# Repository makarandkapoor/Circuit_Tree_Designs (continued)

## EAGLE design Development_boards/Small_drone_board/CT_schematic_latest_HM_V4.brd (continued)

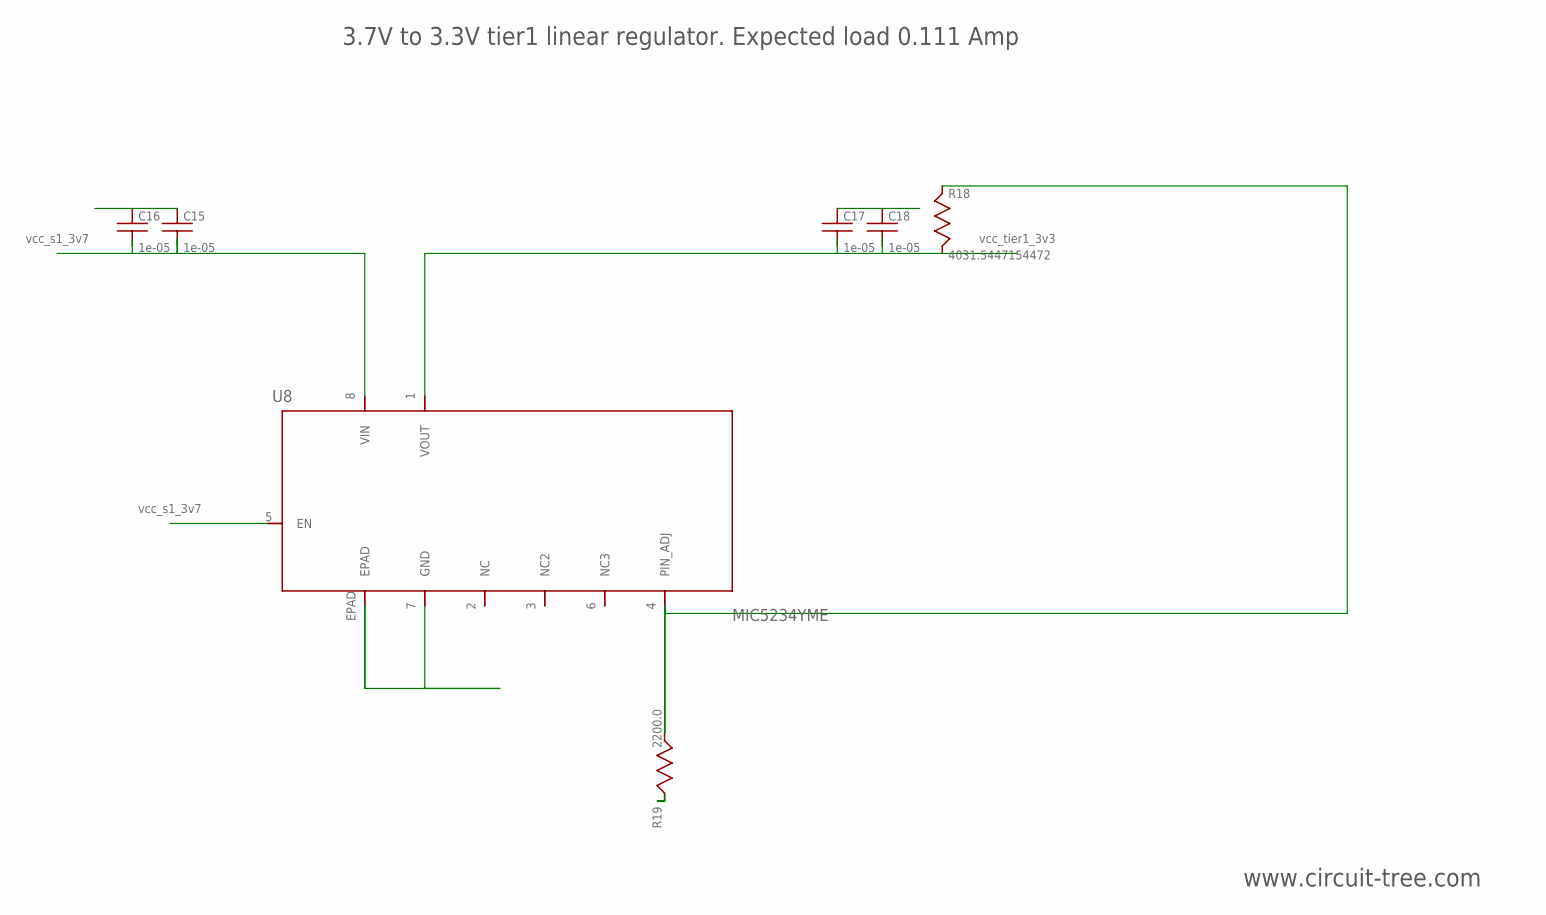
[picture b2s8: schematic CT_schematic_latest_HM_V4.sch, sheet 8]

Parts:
C15, C16, C17, C18: 1e-05; C1210
R18: 4031.5447154472; R0603
R19: 2200.0; R0603
U8: MIC5234YME; SOIC-8_EP

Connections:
GND: C15.2, C16.2, C17.2, C18.2, R19.2, U8.7 (GND), U8.EPAD; also elsewhere on the board
NET_U8_4: R18.2, R19.1, U8.4 (PIN_ADJ)
VCC_S1_3V7: C15.1, C16.1, U8.5 (EN), U8.8 (VIN); also elsewhere on the board
VCC_TIER1_3V3: C17.1, C18.1, R18.1, U8.1 (VOUT); also elsewhere on the board

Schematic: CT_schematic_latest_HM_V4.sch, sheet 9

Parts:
C19: 1e-07; C0402
R20, R21: 10000.0; R0603
R22: 9100.0; R0603
R23: 680000.0; R0603
R24: 120000.0; R0603
U11: TPS3895ADRYR; SON-6

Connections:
GND: C19.2, R22.2, R24.2, U11.2 (GND); also elsewhere on the board
NET_U11_1: R21.1, R22.1, U11.1 (ENABLE)
NET_U11_3: R23.2, R24.1, U11.3 (SENSE)
NET_U11_4: R20.1, U11.4 (SENSE_OUT); also elsewhere on the board
VCC_TIER1_3V3: C19.1, R20.2, R21.2, R23.1, U11.6 (VCC); also elsewhere on the board

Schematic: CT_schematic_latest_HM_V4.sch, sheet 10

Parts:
C20, C21: 1e-05; C1206
R25: 2000.0; R0603
R26: 10000.0; R0603
U9: MCP73831T-2ACI/MC; DFN8_2X3MC
U10: S2B-PH-SM4-TB(LF)(SN); JST-2-SMD

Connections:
GND: C20.2, C21.2, R25.2, U9.6 (VSS), U9.9 (EP), U10.2 (TP2); also elsewhere on the board
INPUT_USBPOWER_5V: C20.1, R26.2, U9.1 (VDD), U9.2 (VDD2); also elsewhere on the board
NET_U9_5: R26.1, U9.5 (STAT)
NET_U9_8: R25.1, U9.8 (PROG)
VCC_S1_3V7: C21.1, U9.3 (VBAT), U9.4 (VBAT2), U10.1 (TP1); also elsewhere on the board

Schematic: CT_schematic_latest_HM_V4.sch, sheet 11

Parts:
C22, C23, C24: 1e-08; C0402
R2: 1000.0; R0603
U12: 4-1437565-2; SW_4-1437565-2
U13: Q65110A2395; LGM67K-G1J2-24-Z
U14, U15, U16: nc7sz125m5x; NC7SZ125M5X

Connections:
GND: C22.2, C23.2, C24.2, R2.2, U13.C, U14.2 (A), U14.3 (GND), U15.1 (OE1_B), U15.3 (GND), U16.1 (OE1_B), U16.3 (GND); also elsewhere on the board
NET_U1_4: U16.4 (Y); also elsewhere on the board
NET_U1_27: U13.A; also elsewhere on the board
NET_U1_28: U12.3 (POLE2), U12.4 (POLE22); also elsewhere on the board
NET_U4_11: U15.4 (Y); also elsewhere on the board
NET_U11_4: U14.4 (Y), U15.2 (A), U16.2 (A); also elsewhere on the board
NET_U12_1: R2.1, U12.1 (POLE1), U12.2 (POLE12)
RST_OUT_U2_JTAG_RST_B: U14.1 (OE1_B); also elsewhere on the board
VCC_TIER1_3V3: C22.1, C23.1, C24.1, U14.5 (VCC), U15.5 (VCC), U16.5 (VCC); also elsewhere on the board

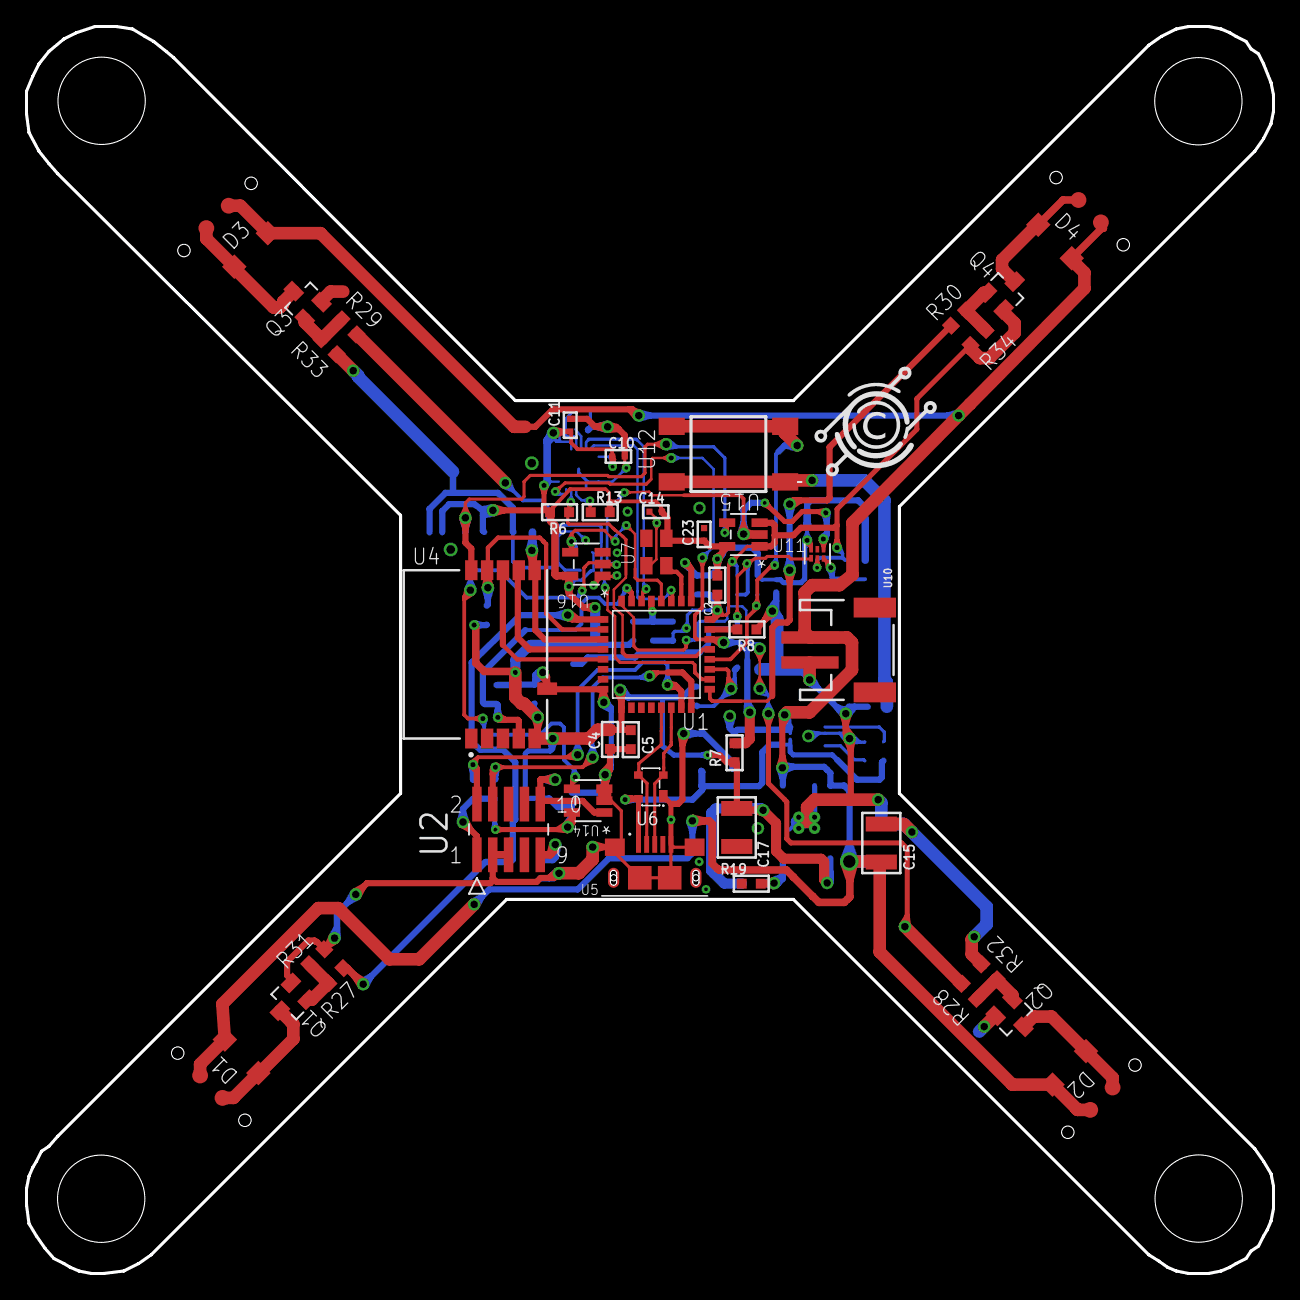
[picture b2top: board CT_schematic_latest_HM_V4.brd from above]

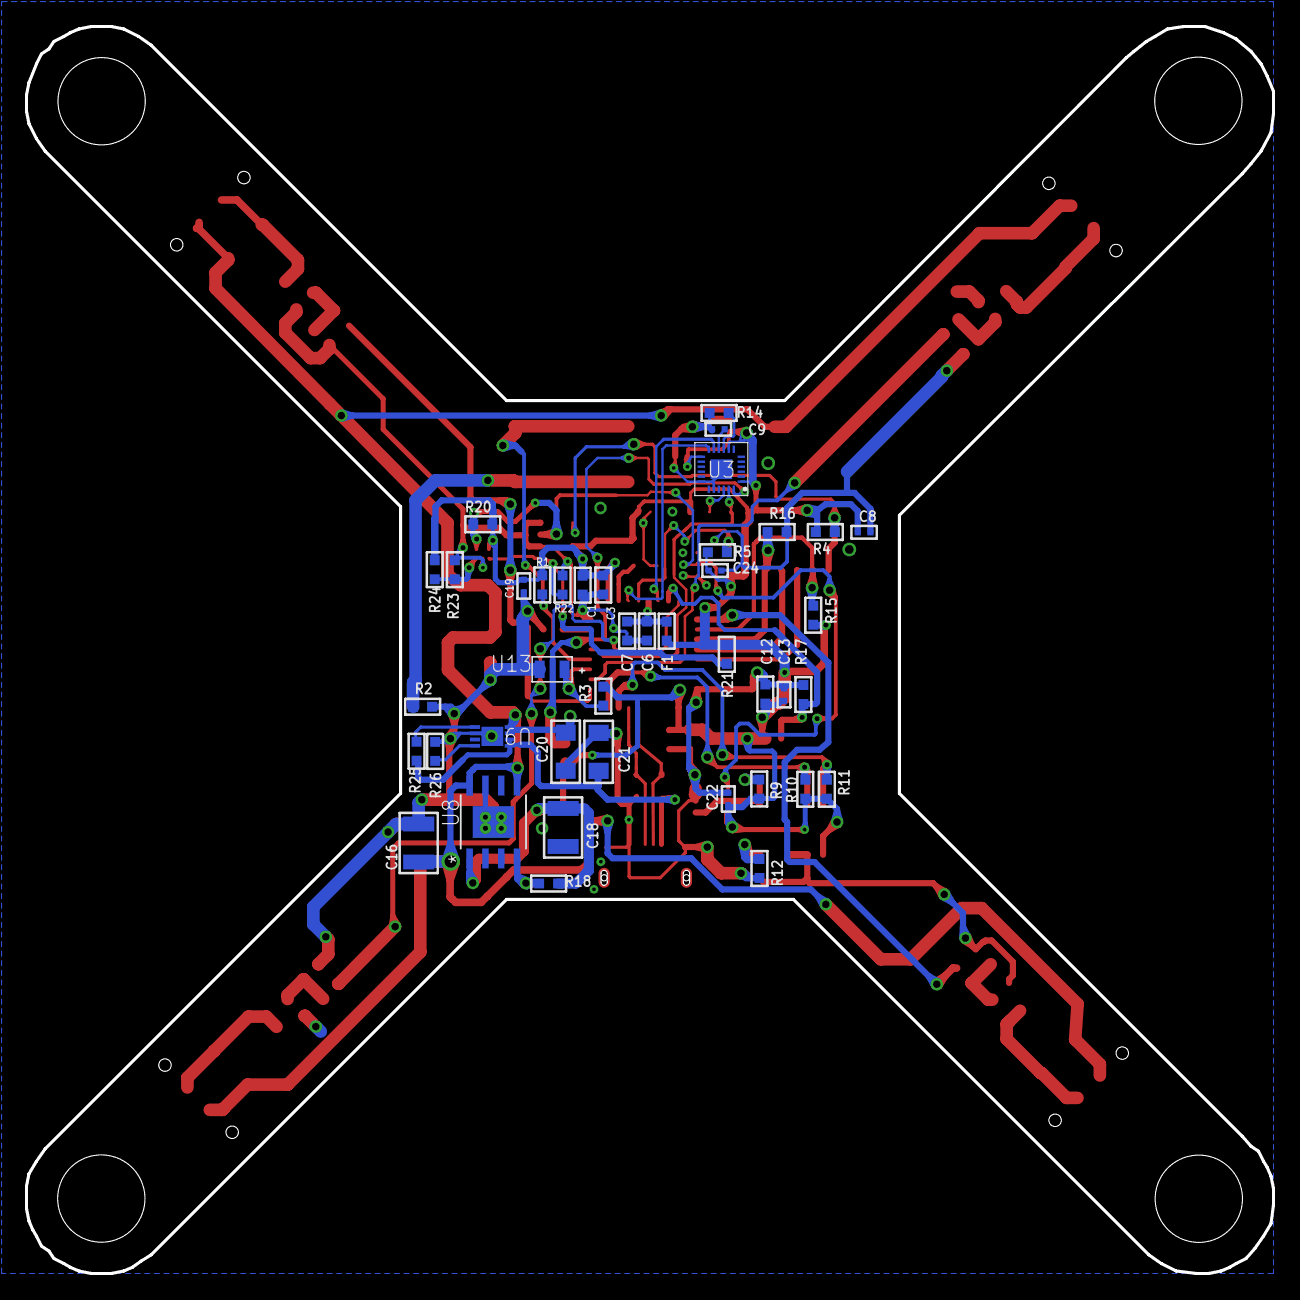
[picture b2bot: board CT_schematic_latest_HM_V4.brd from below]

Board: 2 copper layers, 100.0 x 100.0 mm, 87 parts (41 on the bottom side), 48 nets.

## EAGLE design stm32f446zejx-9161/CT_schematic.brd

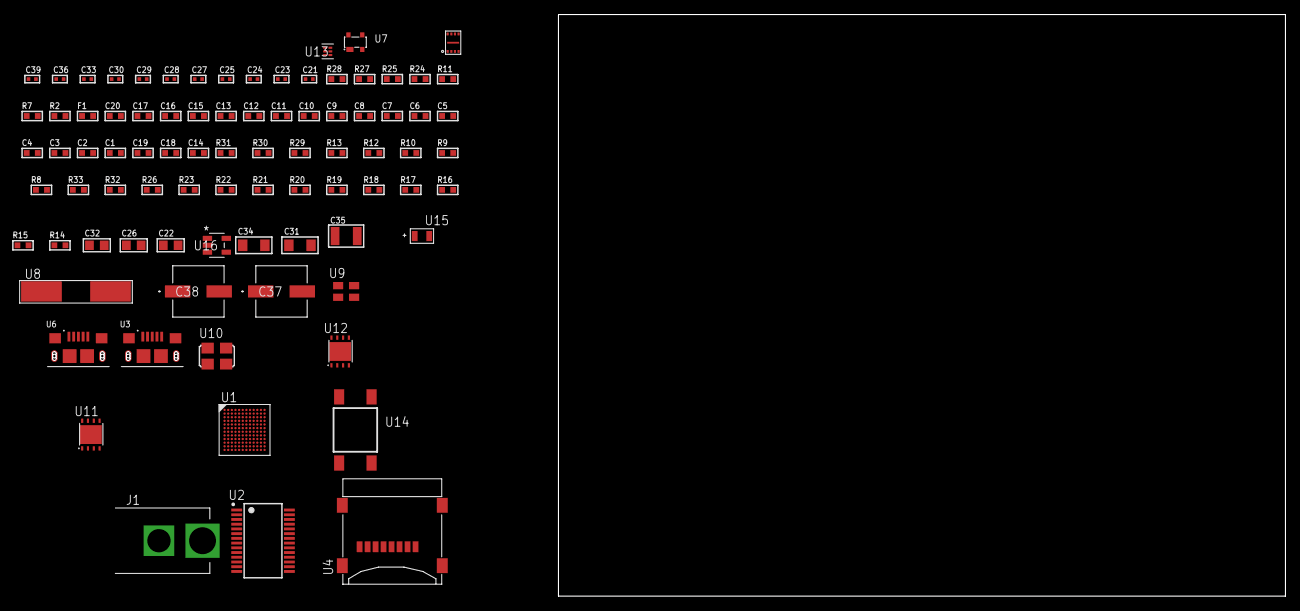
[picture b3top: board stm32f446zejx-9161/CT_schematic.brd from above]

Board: 2 copper layers, 169.6 x 80.0 mm, 85 parts (0 on the bottom side), 51 nets, no tracks yet.

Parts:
C1, C16, C20: 1e-06; C0603
C2, C3, C4, C5, C6, C7, C8, C9, C10, C11, C12, C13, C17: 1e-07; C0603
C14: 4.7e-06; C0603
C15: 1e-08; C0603
C18, C19: 2.2e-06; C0603
C21, C23, C24, C25, C27, C36: 1e-07; C0402
C22: 4.7e-06; C0805
C26, C32: 1e-05; C0805
C28, C29, C30, C33, C39: 1e-08; C0402
C31, C34: 1e-05; C1206
C35: 1e-05; C1210
C37, C38: 0.0001; EXV-9H
F1: 240.0; L0603
J1: PJ-037B; PJ-037B_PACKAGE
R2, R25, R28: 1000.0; R0603
R7, R11: 4700.0; R0603
R8, R9, R10, R12, R13, R29, R30: 10000.0; R0603
R14, R15, R16, R17, R18, R19, R20, R21, R22, R23, R26: 100000.0; R0603
R24: 806.0; R0603
R27: 2231.0; R0603
R31: 82000.0; R0603
R32: 300000.0; R0603
R33: 120000.0; R0603
U1: STM32F446ZEJ7; UFBGA144
U2: FT232RL-REEL; SSOP-28
U3, U6: 10118193-0001LF; FCI_10118193-0001LF
U4: 0472192001; MOLEX_47219-2001
U5: SST26WF040BT-104I/NP; USON-8
U7: prtr5v0u2ax; SOT143B
U8: ABLS-12.000MHZ-B4-T
U9: ASEK-32.768KHz-ECST; ASEK
U10: ASFL1-25MHZ-NCS; ASFL1
U11, U12: LP3878SDX-ADJ/NOPB; WSON-8
U13: TPS3895ADRYR; SON-6
U14: 4-1437565-2; SW_4-1437565-2
U15: Q65110A2395; LGM67K-G1J2-24-Z
U16: nc7sz125m5x; NC7SZ125M5X

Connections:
CLK_CRYSTAL_U2_27: U2.27, U8.1
CLK_CRYSTAL_U2_28: U2.28, U8.2
CLK_U1_B1: U1.B1, U9.3
CLK_U1_D1: U1.D1, U10.3
GND: C1.2, C2.2, C3.2, C4.2, C5.2, C6.2, C7.2, C8.2, C9.2, C10.2, C11.2, C12.2, C13.2, C14.2, C15.2, C16.2, C17.2, C18.2, C19.2, C20.2, C21.2, C22.2, C23.2, C24.2, C25.2, C26.2, C27.2, C28.2, C29.2, C30.2, C31.2, C32.2, C33.2, C34.2, C35.2, C36.2, C37.2, C38.2, C39.2, J1.2, R2.2, R8.2, R10.2, R13.2, R25.2, R28.2, R31.2, R33.2, U1.C12, U1.D2, U1.E6, U1.E7, U1.G4, U1.G8, U1.G10, U1.H6, U1.J1, U1.K1, U2.7, U2.18, U2.21, U2.25, U2.26, U3.5, U3.6, U3.7, U3.8, U3.9, U4.6, U4.G1, U4.G2, U4.G3, U4.G4, U5.4, U5.9, U6.5, U6.6, U6.7, U6.8, U6.9, U7.1, U9.2, U10.2, U11.3, U11.PAD, U12.3, U12.PAD, U13.2, U15.C, U16.1, U16.3
NET_U1_D5: R8.1, U1.D5
NET_U1_E5: R9.1, U1.E5
NET_U1_F1: R7.1, U1.F1, U16.4
NET_U1_G9: C19.1, U1.G9
NET_U1_H5: R10.1, U1.H5
NET_U1_H7: C18.1, U1.H7
NET_U1_M1: C15.1, C16.1, F1.1, U1.L1, U1.M1
NET_U1_M12: U14.3, U14.4
NET_U2_14: R12.1, U2.14
NET_U2_17: C23.1, U2.17
NET_U2_19: R13.1, U2.19
NET_U3_1: R11.1, U3.1
NET_U3_2: U2.16, U3.2
NET_U3_3: U2.15, U3.3
NET_U11_1: C30.1, U11.1
NET_U11_6: R24.2, R25.1, U11.6
NET_U11_8: R23.1, U11.8
NET_U12_1: C33.1, U12.1
NET_U12_6: R27.2, R28.1, U12.6
NET_U12_8: R26.1, U12.8
NET_U13_1: R30.1, R31.1, U13.1
NET_U13_3: R32.2, R33.1, U13.3
NET_U13_4: R29.1, U13.4, U16.2
NET_U14_1: R2.1, U14.1, U14.2
PROC_QUADSPI_BK1_IO0: U1.G3, U5.5
PROC_QUADSPI_BK1_IO1: U1.G2, U5.2
PROC_QUADSPI_BK1_IO2: R21.1, U1.A3, U5.3
PROC_QUADSPI_BK1_IO3: R22.1, U1.F3, U5.7
PROC_QUADSPI_BK1_NCS: R20.1, U1.C6, U5.1
PROC_QUADSPI_CLK: U1.D9, U5.6
PROC_SDIO_CK: R15.1, U1.C10, U4.5
PROC_SDIO_CMD: R14.1, U1.E9, U4.3
PROC_SDIO_D0: R16.1, U1.F11, U4.7
PROC_SDIO_D1: R17.1, U1.E11, U4.8
PROC_SDIO_D2: R18.1, U1.B11, U4.1
PROC_SDIO_D3: R19.1, U1.B10, U4.2
PROC_UART4_CTS: U1.L4, U2.3
PROC_UART4_RTS: U1.A10, U2.11
PROC_UART4_RX: U1.K2, U2.1
PROC_UART4_TX: U1.J2, U2.5
PROC_USB_OTG_FS_DM: U1.C12, U6.2, U7.3
PROC_USB_OTG_FS_DP: U1.B12, U6.3, U7.2
PROC_USB_OTG_FS_VBUS: C20.1, U1.D12, U6.1, U7.4
VCC_S1_9V4: C31.1, C34.1, C37.1, C38.1, J1.1, R23.2, R26.2, U11.4, U12.4
VCC_TIER1_1V8: C1.1, C2.1, C3.1, C4.1, C5.1, C6.1, C7.1, C8.1, C9.1, C10.1, C11.1, C12.1, C13.1, C14.1, C17.1, C24.1, C25.1, C26.1, C27.1, C32.1, C36.1, C39.1, F1.2, R7.2, R9.2, R14.2, R15.2, R16.2, R17.2, R18.2, R19.2, R20.2, R21.2, R22.2, R24.1, R29.2, R30.2, R32.1, U1.C2, U1.C11, U1.D3, U1.F4, U1.F5, U1.F6, U1.F7, U1.F8, U1.F9, U1.F10, U1.G5, U1.G6, U1.G7, U2.4, U4.4, U5.8, U11.5, U13.6, U16.5
VCC_TIER1_3V3: C21.1, C22.1, C28.1, C29.1, C35.1, R12.2, R27.1, U2.20, U9.4, U10.4, U12.5

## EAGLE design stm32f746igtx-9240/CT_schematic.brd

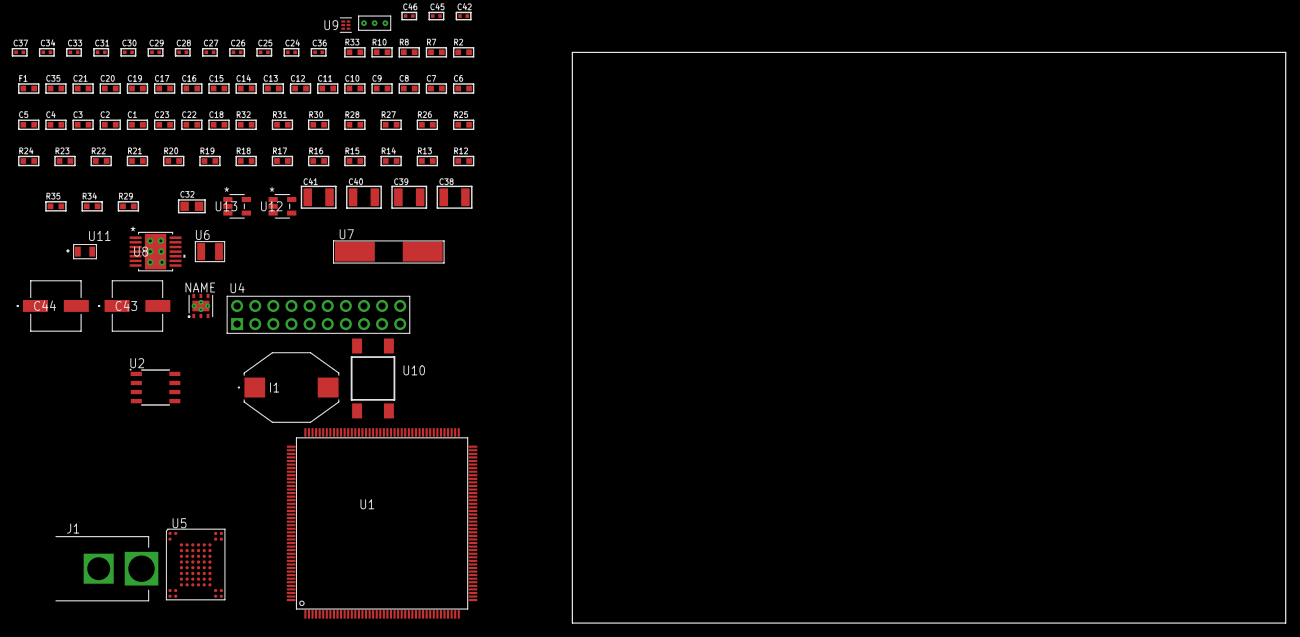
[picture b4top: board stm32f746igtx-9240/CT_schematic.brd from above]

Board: 2 copper layers, 100.0 x 80.0 mm, 91 parts (0 on the bottom side), 56 nets, no tracks yet.

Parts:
C1, C20, C35: 1e-06; C0603
C2, C3, C4, C5, C6, C7, C8, C9, C10, C11, C12, C13, C14, C15, C16, C17, C21: 1e-07; C0603
C18: 4.7e-06; C0603
C19: 1e-08; C0603
C22, C23: 2.2e-06; C0603
C24, C25, C26, C27: 1e-11; C0402
C28, C29, C45, C46: 1e-08; C0402
C30, C31, C33, C34, C37, C42: 1e-07; C0402
C32: 1e-05; C0805
C36: 3.3e-09; C0402
C38, C39: 2.2e-05; C1210
C40, C41: 1e-05; C1210
C43, C44: 0.0001; EXV-9H
F1: 240.0; L0603
I1: 1e-05; IND_PM3316
J1: PJ-037B; PJ-037B_PACKAGE
R2: 1000.0; R0603
R7: 4700.0; R0603
R8, R10: 2200.0; R0603
R12, R13, R14, R15, R16, R17, R18, R19, R20, R21, R22, R23, R24, R25, R26, R27, R28, R31, R32: 10000.0; R0603
R29: 71007.101651032; R0603
R30: 22000.0; R0603
R33: 9100.0; R0603
R34: 680000.0; R0603
R35: 120000.0; R0603
U1: STM32F746IGT7; LQFP176
U2: AT25640B-SSHL-T; SOIC-8
U3: HDC1080DMBR; WSON-6
U4: TST-110-05-T-D-RA
U5: TH58NVG3S0HBAI4
U6: ABS07-32.768KHZ-7-T
U7: ABLS-25.000MHZ-B2F-T
U8: tps54225PWP; HTSSOP14
U9: TPS3895ADRYR; SON-6
U10: 4-1437565-2; SW_4-1437565-2
U11: Q65110A2395; LGM67K-G1J2-24-Z
U12, U13: nc7sz125m5x; NC7SZ125M5X
U14: Dummy; DUMMY_PACKAGE_191

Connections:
CLK_CRYSTAL_U1_9: C24.1, U1.9, U6.1
CLK_CRYSTAL_U1_10: C25.1, U1.10, U6.2
CLK_CRYSTAL_U1_29: C26.1, U1.29, U7.1
CLK_CRYSTAL_U1_30: C27.1, U1.30, U7.2
GND: C1.2, C2.2, C3.2, C4.2, C5.2, C6.2, C7.2, C8.2, C9.2, C10.2, C11.2, C12.2, C13.2, C14.2, C15.2, C16.2, C17.2, C18.2, C19.2, C20.2, C21.2, C22.2, C23.2, C24.2, C25.2, C26.2, C27.2, C28.2, C29.2, C30.2, C31.2, C32.2, C33.2, C34.2, C35.2, C36.2, C38.2, C39.2, C40.2, C41.2, C42.2, C43.2, C44.2, C45.2, C46.2, J1.2, R2.2, R12.2, R14.2, R23.2, R30.2, R33.2, R35.2, U1.14, U1.22, U1.37, U1.61, U1.71, U1.90, U1.102, U1.113, U1.126, U1.135, U1.148, U1.158, U2.4, U3.2, U3.PAD, U4.4, U4.6, U4.8, U4.10, U4.12, U4.14, U4.16, U4.18, U4.20, U5.C5, U5.K3, U5.K8, U8.5, U8.8, U8.9, U8.15, U9.2, U11.C, U12.2, U12.3, U13.1, U13.3, U14.1
NET_U1_31: R7.1, U1.31, U13.4
NET_U1_39: C19.1, C20.1, F1.1, U1.38, U1.39
NET_U1_48: R14.1, U1.48
NET_U1_81: C22.1, U1.81
NET_U1_125: C23.1, U1.125
NET_U1_164: R8.1, U1.164, U3.6
NET_U1_165: R10.1, U1.165, U3.1
NET_U1_166: R12.1, U1.166
NET_U1_171: R13.1, U1.171
NET_U1_176: U10.3, U10.4
NET_U2_3: R15.1, U2.3
NET_U2_7: R17.1, U2.7
NET_U4_19: R23.1, U4.19
NET_U5_C3: R27.1, U5.C3
NET_U8_2: R29.2, R30.1, U8.2
NET_U8_3: C35.1, U8.3
NET_U8_4: C36.1, U8.4
NET_U8_10: C37.1, I1.1, U8.10, U8.11
NET_U8_12: C37.2, U8.12
NET_U9_1: R32.1, R33.1, U9.1
NET_U9_3: R34.2, R35.1, U9.3
NET_U9_4: R31.1, U9.4, U12.4, U13.2
NET_U10_1: R2.1, U10.1, U10.2
PROC_FMC_A16: U1.99, U5.D5
PROC_FMC_A17: U1.100, U5.C4
PROC_FMC_D0: U1.104, U5.H4
PROC_FMC_D1: U1.105, U5.J4
PROC_FMC_D2: U1.142, U5.K4
PROC_FMC_D3: U1.143, U5.K5
PROC_FMC_D4: U1.68, U5.K6
PROC_FMC_D5: U1.69, U5.J7
PROC_FMC_D6: U1.70, U5.K7
PROC_FMC_D7: U1.73, U5.J8
PROC_FMC_INT: R28.1, U1.111, U5.C8
PROC_FMC_NCE: R24.1, U1.152, U5.C6
PROC_FMC_NOE: R25.1, U1.146, U5.D4
PROC_FMC_NWE: R26.1, U1.147, U5.C7
PROC_SPI1_MISO: U1.52, U2.2
PROC_SPI1_MOSI: U1.53, U2.5
PROC_SPI1_NSS: R16.1, U1.50, U2.1
PROC_SPI1_SCK: U1.51, U2.6
PROC_SYS_JTCK_SWCLK: R21.1, U1.137, U4.9
PROC_SYS_JTDI: R19.1, U1.138, U4.5
PROC_SYS_JTDO_SWO: U1.161, U4.13
PROC_SYS_JTMS_SWDIO: R20.1, U1.124, U4.7
PROC_SYS_JTRST: R18.1, U1.162, U4.3
PROC_TIM1_CH2: U1.74, U14.2
PROC_TIM1_CH4: U1.77, U14.3
RST_OUT_U4_SRESET_B: R22.1, U4.15, U12.1
VCC_S1_16V7: C40.1, C41.1, C43.1, C44.1, J1.1, U8.7, U8.13, U8.14
VCC_TIER1_3V3: C1.1, C2.1, C3.1, C4.1, C5.1, C6.1, C7.1, C8.1, C9.1, C10.1, C11.1, C12.1, C13.1, C14.1, C15.1, C16.1, C17.1, C18.1, C21.1, C28.1, C29.1, C30.1, C31.1, C32.1, C33.1, C34.1, C38.1, C39.1, C42.1, C45.1, C46.1, F1.2, I1.2, R7.2, R8.2, R10.2, R13.2, R15.2, R16.2, R17.2, R18.2, R19.2, R20.2, R21.2, R22.2, R24.2, R25.2, R26.2, R27.2, R28.2, R29.1, R31.2, R32.2, R34.1, U1.6, U1.15, U1.23, U1.36, U1.49, U1.62, U1.72, U1.82, U1.91, U1.103, U1.114, U1.127, U1.136, U1.149, U1.159, U1.172, U2.8, U3.5, U4.1, U4.2, U5.H8, U5.J6, U8.1, U9.6, U12.5, U13.5

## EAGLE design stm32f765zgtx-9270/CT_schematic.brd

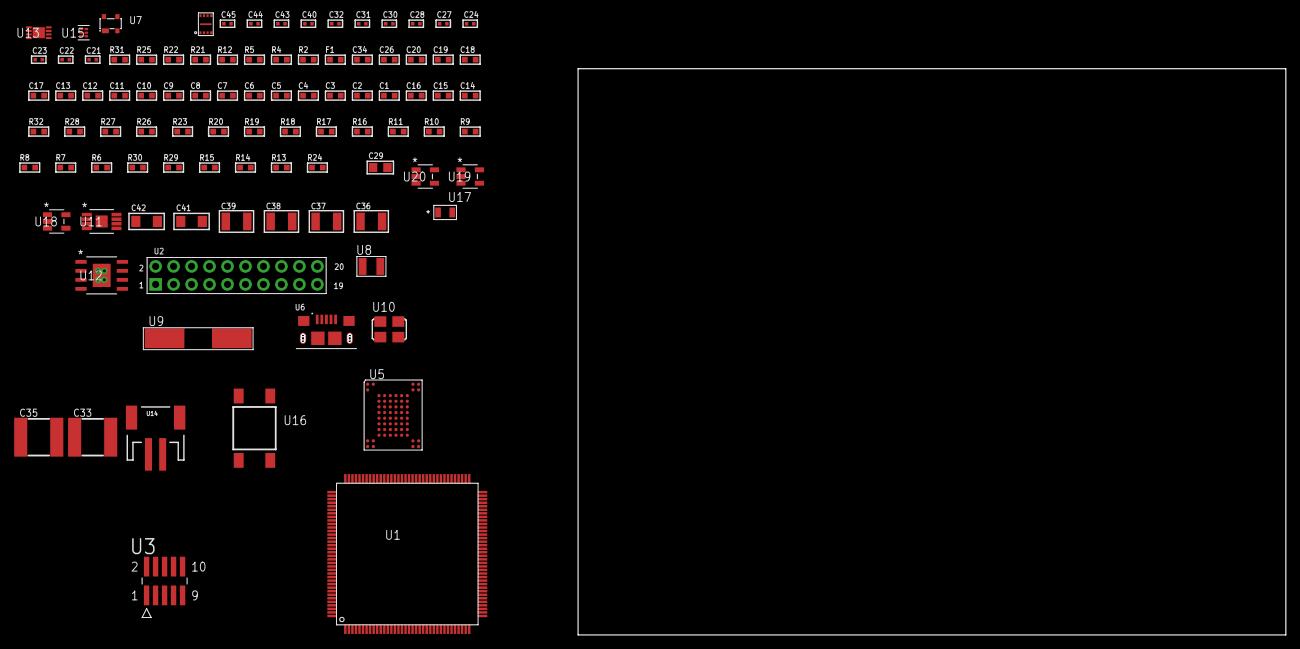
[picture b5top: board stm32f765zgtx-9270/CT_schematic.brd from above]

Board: 2 copper layers, 95 parts (0 on the bottom side), 45 nets, no tracks yet.

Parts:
C1, C18, C26, C34: 1e-06; C0603
C2, C3, C4, C5, C6, C7, C8, C9, C10, C11, C12, C13, C19, C20: 1e-07; C0603
C14: 4.7e-06; C0603
C15, C16: 2.2e-06; C0603
C17: 1e-08; C0603
C21, C22, C23, C24: 1e-11; C0402
C27, C28, C30, C31, C40: 1e-07; C0402
C29: 1e-05; C0805
C32, C43, C44, C45: 1e-08; C0402
C33, C35: 6.8e-05; 2220
C36, C37, C38, C39: 1e-05; C1210
C41, C42: 1e-05; C1206
F1: 240.0; L0603
R2: 1000.0; R0603
R4, R5: 4700.0; R0603
R6, R7, R8, R9, R10, R11, R16, R17, R18, R19, R20, R23, R26, R27, R32: 10000.0; R0603
R12: 5.0; R0603
R13, R14, R15: 100000.0; R0603
R21: 3900.0; R0603
R22, R25: 2200.0; R0603
R24: 4031.5447154472; R0603
R28: 82000.0; R0603
R29: 300000.0; R0603
R30: 120000.0; R0603
R31: 2000.0; R0603
U1: STM32F765ZGT7; LQFP144
U2: arducam_ov2640; ARDUCAM
U3: FTSH-105-01-L-DV-K; SAMTEC_FTSH-105-01-L-DV-K
U4: SST26WF080BT-104I/NP; USON-8
U5: TH58NVG3S0HBAI4
U6: 10118193-0001LF; FCI_10118193-0001LF
U7: prtr5v0u2ax; SOT143B
U8: ABS07-32.768KHZ-7-T
U9: ABLS-25.000MHZ-B2F-T
U10: ASFL1-25MHZ-NCS; ASFL1
U11: MIC47100YMME; MSOP-8_EP
U12: MIC5234YME; SOIC-8_EP
U13: MCP73831T-2ACI/MC; DFN8_2X3MC
U14: S2B-PH-SM4-TB(LF)(SN); JST-2-SMD
U15: TPS3895ADRYR; SON-6
U16: 4-1437565-2; SW_4-1437565-2
U17: Q65110A2395; LGM67K-G1J2-24-Z
U18, U19, U20: nc7sz125m5x; NC7SZ125M5X

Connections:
CLK_CRYSTAL_U1_8: C21.1, U1.8, U8.1
CLK_CRYSTAL_U1_9: C22.1, U1.9, U8.2
CLK_CRYSTAL_U1_23: C23.1, U1.23, U9.1
CLK_CRYSTAL_U1_24: C24.1, U1.24, U9.2
CLK_U2_8: U2.8, U10.3
GND: C1.2, C2.2, C3.2, C4.2, C5.2, C6.2, C7.2, C8.2, C9.2, C10.2, C11.2, C12.2, C13.2, C14.2, C15.2, C16.2, C17.2, C18.2, C19.2, C20.2, C21.2, C22.2, C23.2, C24.2, C26.2, C27.2, C28.2, C29.2, C30.2, C31.2, C32.2, C33.2, C34.2, C35.2, C36.2, C37.2, C38.2, C39.2, C40.2, C41.2, C42.2, C43.2, C44.2, C45.2, R2.2, R6.2, R11.2, R12.2, R22.2, R25.2, R28.2, R30.2, R31.2, U1.16, U1.31, U1.38, U1.51, U1.61, U1.83, U1.94, U1.107, U1.120, U1.130, U2.2, U2.20, U3.3, U3.5, U4.4, U4.9, U5.C5, U5.K3, U5.K8, U6.5, U6.6, U6.7, U6.8, U6.9, U7.1, U10.2, U11.3, U11.EPAD, U12.7, U12.EPAD, U13.6, U13.9, U14.2, U15.2, U17.C, U18.2, U18.3, U19.1, U19.3, U20.1, U20.3
INPUT_USBPOWER_5V: C41.1, R32.2, U6.1, U7.4, U13.1, U13.2
NET_U1_25: R4.1, U1.25, U19.4
NET_U1_33: C17.1, C18.1, F1.1, U1.32, U1.33
NET_U1_71: C15.1, U1.71
NET_U1_106: C16.1, U1.106
NET_U1_138: R6.1, U1.138
NET_U1_142: U16.3, U16.4
NET_U1_143: R7.1, U1.143
NET_U2_19: R5.1, U2.19, U20.4
NET_U3_9: R12.1, U3.9
NET_U5_C3: R19.1, U5.C3
NET_U5_C6: R16.1, U5.C6
NET_U5_C7: R18.1, U5.C7
NET_U5_C8: R20.1, U5.C8
NET_U5_D4: R17.1, U5.D4
NET_U11_6: R21.2, R22.1, U11.6
NET_U12_4: R24.2, R25.1, U12.4
NET_U13_5: R32.1, U13.5
NET_U13_8: R31.1, U13.8
NET_U15_1: R27.1, R28.1, U15.1
NET_U15_3: R29.2, R30.1, U15.3
NET_U15_4: R26.1, U15.4, U18.4, U19.2, U20.2
NET_U16_1: R2.1, U16.1, U16.2
PROC_QUADSPI_BK1_IO0: U1.20, U4.5
PROC_QUADSPI_BK1_IO1: U1.21, U4.2
PROC_QUADSPI_BK1_IO2: R14.1, U1.1, U4.3
PROC_QUADSPI_BK1_IO3: R15.1, U1.18, U4.7
PROC_QUADSPI_BK1_NCS: R13.1, U1.69, U4.1
PROC_QUADSPI_CLK: U1.22, U4.6
PROC_SYS_JTCK_SWCLK: R11.1, U1.109, U3.4
PROC_SYS_JTDI: R9.1, U1.110, U3.8
PROC_SYS_JTDO_SWO: U1.133, U3.6
PROC_SYS_JTMS_SWDIO: R10.1, U1.105, U3.2
PROC_USB_OTG_FS_DM: U6.2, U7.3
PROC_USB_OTG_FS_DP: U6.3, U7.2
RST_OUT_U3_JTAG_RST_B: R8.1, U3.10, U18.1
VCC_S1_3V7: C33.1, C34.1, C36.1, C37.1, C42.1, R23.1, R23.2, U11.1, U11.2, U11.4, U11.5, U12.5, U12.8, U13.3, U13.4, U14.1
VCC_TIER1_1V8: C1.1, C2.1, C3.1, C4.1, C5.1, C6.1, C7.1, C8.1, C9.1, C10.1, C11.1, C12.1, C13.1, C14.1, C19.1, C20.1, C27.1, C28.1, C35.1, C40.1, C43.1, C44.1, C45.1, F1.2, R4.2, R7.2, R8.2, R9.2, R10.2, R13.2, R14.2, R15.2, R21.1, R26.2, R27.2, R29.1, U1.6, U1.17, U1.30, U1.39, U1.52, U1.62, U1.72, U1.84, U1.95, U1.108, U1.121, U1.131, U1.144, U3.1, U4.8, U11.7, U11.8, U15.6, U18.5, U19.5, U20.5
VCC_TIER1_3V3: C26.1, C29.1, C30.1, C31.1, C32.1, C38.1, C39.1, R5.2, R16.2, R17.2, R18.2, R19.2, R20.2, R24.1, U2.1, U5.H8, U5.J6, U10.4, U12.1

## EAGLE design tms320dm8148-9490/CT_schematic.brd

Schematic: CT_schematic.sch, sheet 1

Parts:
C1, C2, C3, C4: 1.2e-11; C0402
C5, C6, C7, C8, C21, C22, C23, C24, C25, C26, C27, C28, C29, C30, C42, C43, C44, C45, C46, C47, C48, C49, C50, C51, C52, C53, C54, C55, C56, C57, C58, C59, C60, C61, C62, C63, C65, C66, C67, C68, C69, C70, C71, C73, C74, C75, C76, C77, C78, C79, C80, C82, C83, C84, C85, C86: 1e-07; C0402
C9, C10, C11, C12, C13, C14, C15, C16, C17, C18, C19: 1e-06; C0603
C20, C41, C64, C72, C81, C87, C98, C109: 1e-05; C0805
C31, C32, C33, C34, C35, C36, C37, C38, C39, C40, C88, C89, C90, C91, C92, C93, C94, C95, C96, C97, C99, C100, C101, C102, C103, C104, C105, C106, C107, C108, C110, C111, C112, C113, C114, C115, C116, C117, C118, C119, C120, C121, C122, C123, C124, C125, C126, C127, C128, C129, C130, C131, C132, C133: 1e-08; C0402
R3, R4, R30: 4700.0; R0603
R9, R10, R11, R12, R13, R17, R18, R19, R20, R21, R22, R23, R24, R25, R26, R27: 10000.0; R0603
R14, R15: 49.9; R0603
R16: 0.1; R0603
R28, R29: 2700.0; R0603
u1: tms320dm8148SCYE2; BFBGA-684
u2: MD-40S

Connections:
CLK_CRYSTAL_U1_AH2: C1.1, u1.AH2 (devosc_mxi); also elsewhere on the board
CLK_CRYSTAL_U1_AH3: C2.1, u1.AH3 (devosc_mxo); also elsewhere on the board
CLK_CRYSTAL_U1_R1: C3.1, u1.R1 (auxosc_mxi); also elsewhere on the board
CLK_CRYSTAL_U1_T1: C4.1, u1.T1 (auxosc_mxo); also elsewhere on the board
NET_U1_AA4: R4.1
NET_U1_AA27: R12.1, u1.AA27 (btmode_11); also elsewhere on the board
NET_U1_AA28: R11.1, u1.AA28 (btmode_5); also elsewhere on the board
NET_U1_AB27: R16.1, u1.AB27 (gpmc_a22); also elsewhere on the board
NET_U1_AB28: R22.1, u1.AB28 (btmode_9); also elsewhere on the board
NET_U1_AG22: R29.2, u1.AG22 (tv_vfb1); also elsewhere on the board
NET_U1_AG23: R28.2, u1.AG23 (tv_vfb0); also elsewhere on the board
NET_U1_AH23: R30.1, u1.AH23 (tv_reset); also elsewhere on the board
NET_U1_B1: R15.1, u1.B1 (ddr1_vtp); also elsewhere on the board
NET_U1_B27: R14.1, u1.B27 (ddr0_vtp); also elsewhere on the board
NET_U1_G14: C7.1, C8.1, u1.G14 (vrefsstl_ddr1); also elsewhere on the board
NET_U1_G15: C5.1, C6.1, u1.G15 (vrefsstl_ddr0); also elsewhere on the board
NET_U1_J5: R3.1, u1.J5 (reset_b); also elsewhere on the board
NET_U1_L18: C13.1, u1.L18 (ldocap_ram2); also elsewhere on the board
NET_U1_M11: C15.1, u1.M11 (ldocap_dspram); also elsewhere on the board
NET_U1_N10: C16.1, u1.N10 (ldocap_hdvicp); also elsewhere on the board
NET_U1_N11: C17.1, u1.N11 (ldocap_hdvicpram); also elsewhere on the board
NET_U1_P10: C14.1, u1.P10 (ldocap_dsp); also elsewhere on the board
NET_U1_P18: C11.1, u1.P18 (ldocap_ram0); also elsewhere on the board
NET_U1_R11: C12.1, u1.R11 (ldocap_ram1); also elsewhere on the board
NET_U1_T10: C18.1, u1.T10 (ldocap_sgx); also elsewhere on the board
NET_U1_T11: C19.1, u1.T11 (ldocap_serdesclk); also elsewhere on the board
NET_U1_U23: R27.1, u1.U23 (btmode_13); also elsewhere on the board
NET_U1_U24: R25.1, u1.U24 (btmode_12); also elsewhere on the board
NET_U1_U25: R10.1, u1.U25 (btmode_6); also elsewhere on the board
NET_U1_U26: R17.1, u1.U26 (btmode_0); also elsewhere on the board
NET_U1_V14: C10.1, u1.V14 (ldocap_armram); also elsewhere on the board
NET_U1_V24: R26.1, u1.V24 (btmode_14); also elsewhere on the board
NET_U1_V25: R9.1, u1.V25 (btmode_7); also elsewhere on the board
NET_U1_V26: R21.1, u1.V26 (btmode_4); also elsewhere on the board
NET_U1_V27: R19.1, u1.V27 (btmode_2); also elsewhere on the board
NET_U1_W14: C9.1, u1.W14 (ldocap_arm); also elsewhere on the board
NET_U1_W27: R20.1, u1.W27 (btmode_3); also elsewhere on the board
NET_U1_Y25: R13.1, u1.Y25 (btmode_15); also elsewhere on the board
NET_U1_Y26: R24.1, u1.Y26 (btmode_10); also elsewhere on the board
NET_U1_Y27: R23.1, u1.Y27 (btmode_8); also elsewhere on the board
NET_U1_Y28: R18.1, u1.Y28 (btmode_1); also elsewhere on the board
NET_U2_3: R28.1; also elsewhere on the board
NET_U2_4: R29.1; also elsewhere on the board
unnamed: u1.AA15 (dvdd), u1.AA17 (dvdd2), u1.AB14 (dvdd3), u1.AB16 (dvdd4), u1.M8 (dvdd5), u1.N7 (dvdd6), u1.P8 (dvdd7), u1.T7 (dvdd8), u1.U21 (dvdd9), u1.U22 (dvdd10), u1.V20 (dvdd11), u1.Y11 (dvdd12), u1.Y16 (dvdd13)
unnamed: u1.AH22 (tv_out1), u2.4 (chrominance)
unnamed: u1.AH24 (tv_out0), u2.3 (luminance)
unnamed: u1.K9 (cvdd3), u1.K12 (cvdd), u1.K18 (cvdd2), u1.L15 (cvdd4), u1.L17 (cvdd5), u1.L19 (cvdd6), u1.M16 (cvdd7), u1.M18 (cvdd8), u1.N17 (cvdd9), u1.N19 (cvdd10), u1.P12 (cvdd11), u1.P14 (cvdd12), u1.P16 (cvdd13), u1.R15 (cvdd14), u1.R17 (cvdd15), u1.R19 (cvdd16), u1.T12 (cvdd17), u1.U11 (cvdd18), u1.U13 (cvdd19), u1.U17 (cvdd20), u1.U19 (cvdd21), u1.W11 (cvdd22)
unnamed: u1.U9 (vdda_sata_1p82), u1.U10 (vdda_sata_1p8)
unnamed: u1.W9 (vdda_pcie_1p82), u1.W10 (vdda_pcie_1p8)
unnamed: u1.W19 (dvdd_c), u1.W20 (dvdd_c2)
VCC_TIER1_1V35: C41.1, C42.1, C43.1, C44.1, C45.1, C46.1, C47.1, C48.1, C49.1, C50.1, C51.1, C52.1, C53.1, C54.1, C55.1, C56.1, C57.1, C58.1, C59.1, C60.1, C61.1, C62.1, C63.1, C64.1, C65.1, C66.1, C67.1, C68.1, C69.1, C70.1, C71.1, C72.1, C73.1, C74.1, C75.1, C76.1, C77.1, C78.1, C79.1, C80.1, C81.1, C82.1, C83.1, C84.1, C85.1, C86.1, u1.K9 (cvdd3), u1.K10 (cvdd_dsp), u1.L9 (cvdd_dsp5), u1.L10 (cvdd_dsp2), u1.L11 (cvdd_dsp3), u1.L12 (cvdd_dsp4), u1.L14 (cvdd_hdvicp), u1.L15 (cvdd4), u1.M10 (cvdd_dsp6), u1.M12 (cvdd_dsp7), u1.M13 (cvdd_hdvicp2), u1.M14 (cvdd_hdvicp3), u1.N9 (cvdd_dsp8), u1.N13 (cvdd_hdvicp4), u1.N14 (cvdd_hdvicp5), u1.T14 (cvdd_arm), u1.T15 (cvdd_arm2), u1.T16 (cvdd_arm3), u1.U15 (cvdd_arm4), u1.U16 (cvdd_arm5), u1.V15 (cvdd_arm6), u1.V16 (cvdd_arm7); also elsewhere on the board
VCC_TIER4_3V3: C40.1, u1.AA13 (vdda_usb_3p3); also elsewhere on the board

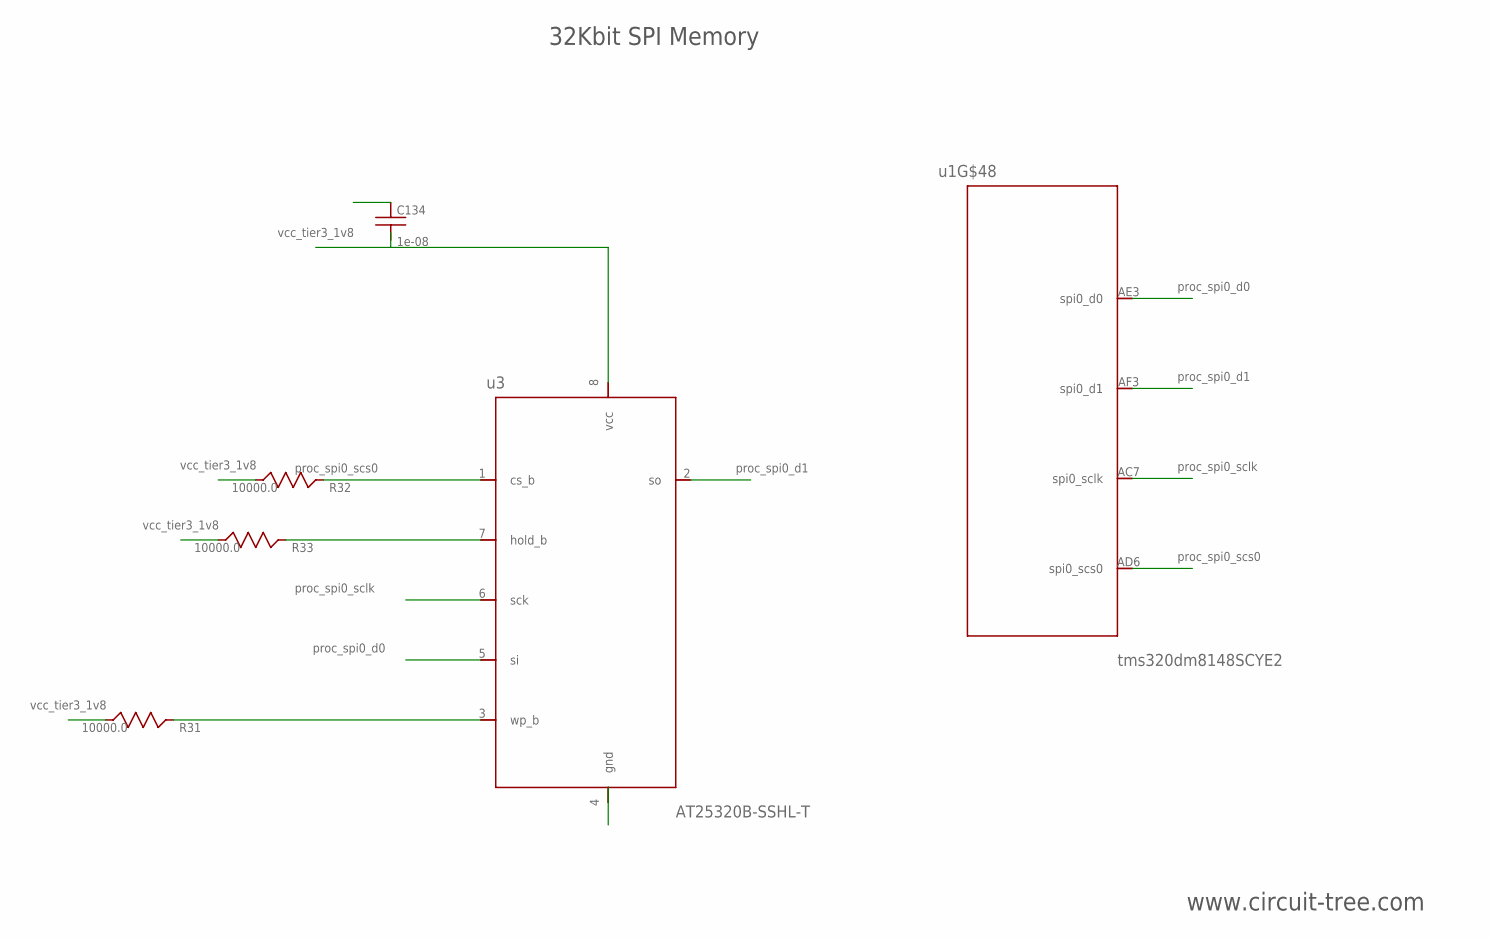
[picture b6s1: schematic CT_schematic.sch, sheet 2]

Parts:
C134: 1e-08; C0402
R31, R32, R33: 10000.0; R0603
u1: tms320dm8148SCYE2; BFBGA-684
u3: AT25320B-SSHL-T; SOIC-8

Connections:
NET_U3_3: R31.1, u3.3 (wp_b); also elsewhere on the board
NET_U3_7: R33.1, u3.7 (hold_b); also elsewhere on the board
unnamed: u1.AC7 (spi0_sclk), u3.6 (sck)
unnamed: u1.AE3 (spi0_d0), u3.5 (si)
unnamed: u1.AF3 (spi0_d1), u3.2 (so)
PROC_SPI0_SCS0: R32.1, u1.AD6 (spi0_scs0), u3.1 (cs_b); also elsewhere on the board
